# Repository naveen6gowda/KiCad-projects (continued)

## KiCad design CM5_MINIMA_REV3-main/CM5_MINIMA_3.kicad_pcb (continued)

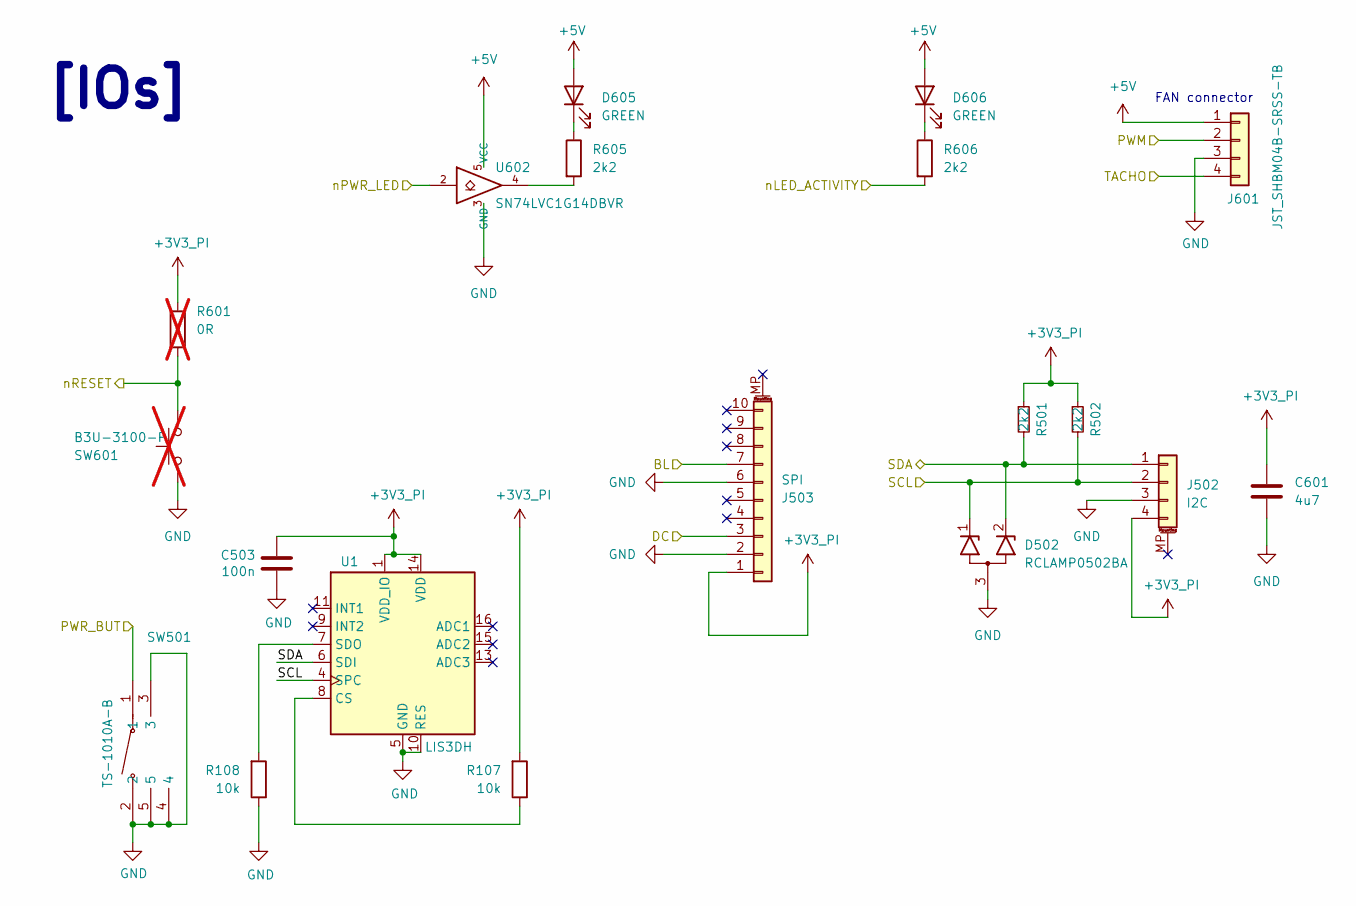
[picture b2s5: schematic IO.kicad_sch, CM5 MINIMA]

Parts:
C503: 100n; C_0402_1005Metric; Part Description 0.1uF 10% 16V Ceramic Capacitor X7R 040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
C601: 4u7; C_0805_2012Metric; Part Description 4.7uF 10% 10V Ceramic Capacitor X7R 080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
D502: RCLAMP0502BA; SOT-416
D605, D606: GREEN; LED-SMD_L1.7-W0.6-RD
J502: I2C; JST_SH_BM04B-SRSS-TB_1x04-1MP_P1.00mm_Vertical
J503: SPI; JST_SUR_BM10B-SURS-TF_1x10-1MP_P0.80mm_Vertical
J601: JST_SHBM04B-SRSS-TB; JST_SH_BM04B-SRSS-TB_1x04-1MP_P1.00mm_Vertical; Part Description 4 pin vertical 1mm pitch connector
R107, R108: 10k; R_0402_1005Metric
R501, R502, R605, R606: 2k2; R_0402_1005Metric
R601: 0R; R_0402_1005Metric; not fitted
SW501: TS-1010A-B; SW-SMD_TS-1010A-B; LCSC Part C381059
SW601: B3U-3100-P; SW_SPST_B3U-3100P-B; not fitted
U1: LIS3DH; LGA-16_3x3mm_P0.5mm_LayoutBorder3x5y
U602: SN74LVC1G14DBVR; SOT-353_SC-70-5; Part Description Buffer, Non-Inverting 1 Element 1 Bit p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

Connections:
+3V3_PI: C503.1, C601.1, J502.4, J503.1, R107.2, R501.1, R502.1, R601.1, U1.1 (VDD_IO), U1.14 (VDD); also elsewhere on the board
+5V: D605.2 (A), D606.2 (A), J601.1, U602.5 (VCC); also elsewhere on the board
/CM5/BL_GPIO24: J503.7; also elsewhere on the board
/CM5/DC_GPI25: J503.3; also elsewhere on the board
/CM5/PI_nLED_PWR: U602.2; also elsewhere on the board
/CM5/PWM: J601.2; also elsewhere on the board
/CM5/PWR_BUT: SW501.1; also elsewhere on the board
/CM5/TACHO: J601.4; also elsewhere on the board
/CM5/nLED_ACTIVITY: R606.2; also elsewhere on the board
/IO/SCL: D502.1 (K1), J502.2, R502.2, U1.4 (SPC); also elsewhere on the board
/IO/SDA: D502.2 (K2), J502.1, R501.2, U1.6 (SDI); also elsewhere on the board
unnamed: D605.1 (K), R605.1
unnamed: D606.1 (K), R606.1
unnamed: R601.2, SW601.1
unnamed: R605.2, U602.4
unnamed: R107.1, U1.8 (CS)
unnamed: R108.2, U1.7 (SDO)

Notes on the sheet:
[IOs]
FAN connector

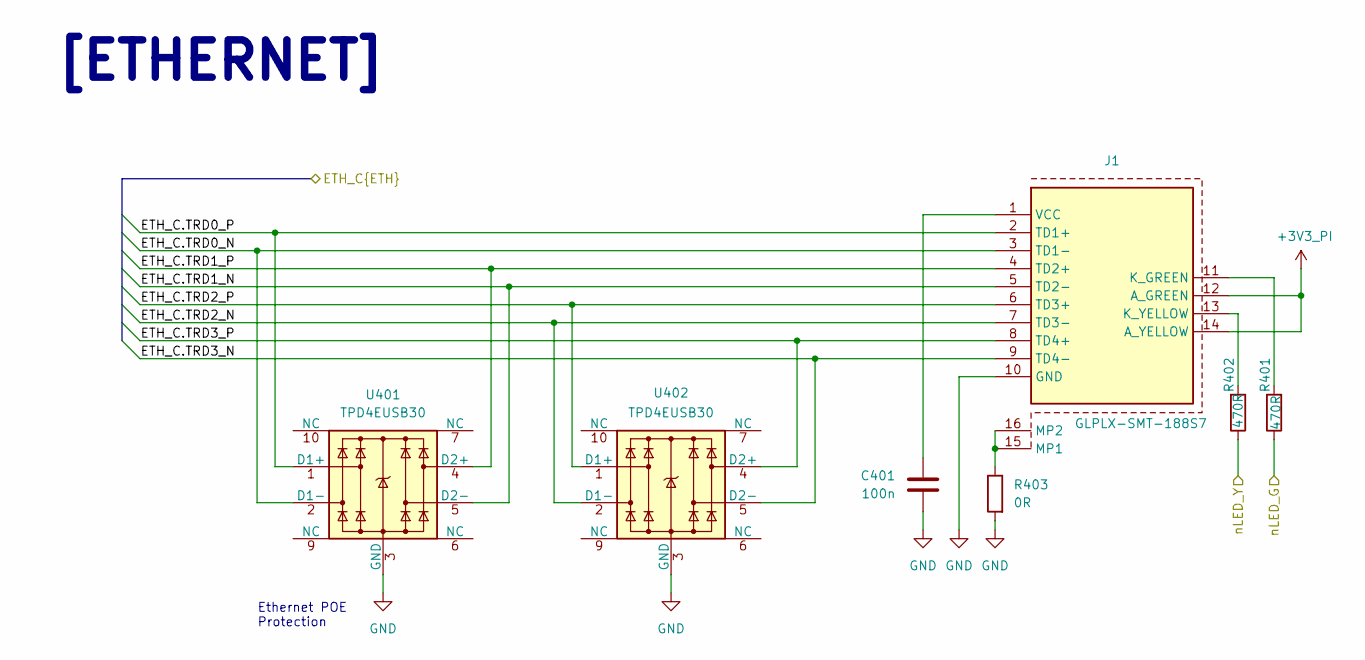
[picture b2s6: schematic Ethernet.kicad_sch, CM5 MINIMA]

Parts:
C401: 100n; C_0402_1005Metric; Part Description 0.1uF 10% 16V Ceramic Capacitor X7R 040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
J1: GLPLX-SMT-188S7; GLPLXSMT188S7QQYG; Manufacturer_Part_Number GLPLX-SMT-188S7-QQ-Y/G; Mouser Part Number 806-GLPLXSMT188S7-YG
R401, R402: 470R; R_0402_1005Metric; LCSC C25117
R403: 0R; R_0402_1005Metric
U401, U402: TPD4EUSB30; USON-10_2.5x1.0mm_P0.5mm; Part Description Quad TVS diode for high speed signals (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

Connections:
+3V3_PI: J1.12 (A_GREEN), J1.14 (A_YELLOW); also elsewhere on the board
/CM5/ETH_PI.TRD0_N: J1.3 (TD1-), U401.2 (D1-), U401.9 (NC); also elsewhere on the board
/CM5/ETH_PI.TRD0_P: J1.2 (TD1+), U401.1 (D1+), U401.10 (NC); also elsewhere on the board
/CM5/ETH_PI.TRD1_N: J1.5 (TD2-), U401.5 (D2-), U401.6 (NC); also elsewhere on the board
/CM5/ETH_PI.TRD1_P: J1.4 (TD2+), U401.4 (D2+), U401.7 (NC); also elsewhere on the board
/CM5/ETH_PI.TRD2_N: J1.7 (TD3-), U402.2 (D1-), U402.9 (NC); also elsewhere on the board
/CM5/ETH_PI.TRD2_P: J1.6 (TD3+), U402.1 (D1+), U402.10 (NC); also elsewhere on the board
/CM5/ETH_PI.TRD3_N: J1.9 (TD4-), U402.5 (D2-), U402.6 (NC); also elsewhere on the board
/CM5/ETH_PI.TRD3_P: J1.8 (TD4+), U402.4 (D2+), U402.7 (NC); also elsewhere on the board
/CM5/ETH_nLED_ACTIVITY: R401.1; also elsewhere on the board
/CM5/nLED_SPEED_100_1000: R402.1; also elsewhere on the board
unnamed: J1.11 (K_GREEN), R401.2
unnamed: J1.13 (K_YELLOW), R402.2
unnamed: J1.15 (MP1), J1.16 (MP2), R403.1
unnamed: C401.1, J1.1 (VCC)

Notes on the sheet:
[ETHERNET]
Ethernet POE Protection

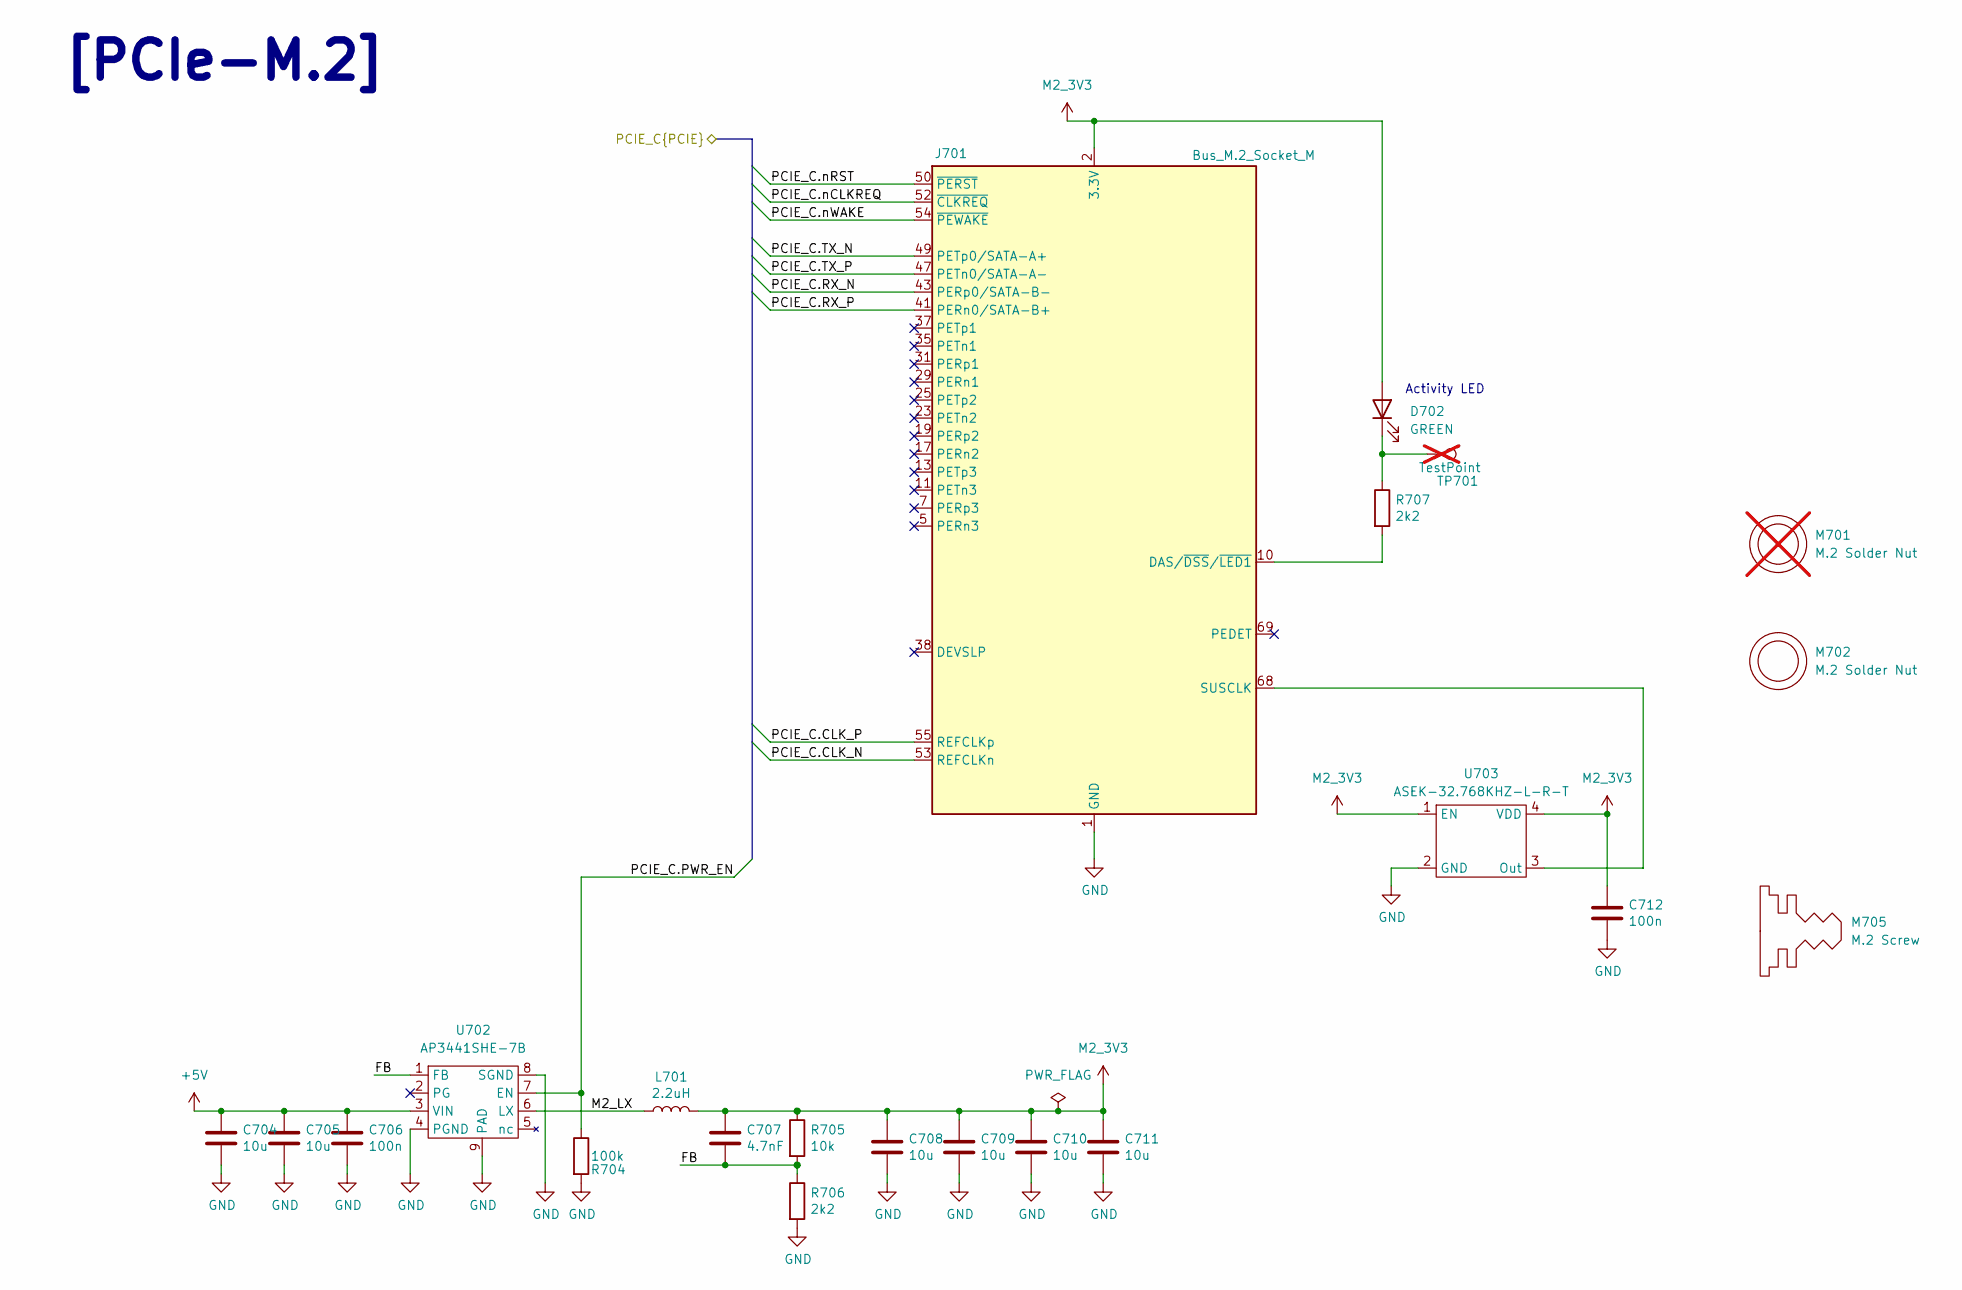
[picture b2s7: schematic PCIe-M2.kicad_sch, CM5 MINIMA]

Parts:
C704, C705, C708, C709, C710, C711: 10u; C_0805_2012Metric; Part Description 10uF 10% 10V Ceramic Capacitor X7R 0805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; LCSC C15850
C706, C712: 100n; C_0402_1005Metric; Part Description 0.1uF 10% 16V Ceramic Capacitor X7R 040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
C707: 4.7nF; C_0402_1005Metric; Part Description 4.7nF capacitor 0402
D702: GREEN; LED-SMD_L1.7-W0.6-RD
J701: Bus_M.2_Socket_M; M.2 M Key socket_2230_2242; Part Description M.2 M Key connector
L701: 2.2uH; L_Coilcraft_XAL5030-XXX; Part Description Inductor, SMT, 2u2, IRMS=7A, ISAT=8.1A,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; LCSC C920280
M701: M.2 Solder Nut; MountingHole_3mm_Pad; Part Description Solder nut for M.2 slot; not fitted
M702: M.2 Solder Nut; MountingHole_3mm_Pad; Part Description Solder nut for M.2 slot
M705: M.2 Screw; Part Description M.2 Screw
R704: 100k; R_0402_1005Metric; LCSC C25741
R705: 10k; R_0402_1005Metric; LCSC C25744
R706: 2k2; R_0402_1005Metric
R707: 2k2; R_0402_1005Metric; Part Description Resistor 1K M1005 1% 63mW
TP701: TestPoint; TestPoint_Pad_2.0x2.0mm; Part Description Test point; not fitted
U702: AP3441SHE-7B; DFN-8-1EP_2x2mm_P0.5mm_EP1.05x1.75mm; Part Description 3A DC-DC converter
U703: ASEK-32.768KHZ-L-R-T; Crystal_SMD_3225-4Pin_3.2x2.5mm; Part Description 32KHz Xtal oscilator

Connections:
+5V: C704.1, C705.1, C706.1, U702.3 (VIN); also elsewhere on the board
/CM5/PCIE_PI.CLK_N: J701.53 (REFCLKn); also elsewhere on the board
/CM5/PCIE_PI.CLK_P: J701.55 (REFCLKp); also elsewhere on the board
/CM5/PCIE_PI.PWR_EN: R704.1, U702.7 (EN); also elsewhere on the board
/CM5/PCIE_PI.RX_N: J701.43 (PETp0); also elsewhere on the board
/CM5/PCIE_PI.RX_P: J701.41 (PETn0); also elsewhere on the board
/CM5/PCIE_PI.TX_N: J701.49 (PERp0); also elsewhere on the board
/CM5/PCIE_PI.TX_P: J701.47 (PERn0); also elsewhere on the board
/CM5/PCIE_PI.nCLKREQ: J701.52 (~CLKREQ); also elsewhere on the board
/CM5/PCIE_PI.nRST: J701.50 (~PERST); also elsewhere on the board
/CM5/PCIE_PI.nWAKE: J701.54 (~PEWAKE); also elsewhere on the board
/PCIe-M2/FB: C707.2, R705.2, R706.1, U702.1 (FB)
/PCIe-M2/M2_LX: L701.1, U702.6 (LX)
M2_3V3: C707.1, C708.1, C709.1, C710.1, C711.1, C712.1, D702.2 (A), J701.2 (3.3V), J701.4 (3.3V), J701.12 (3.3V), J701.14 (3.3V), J701.16 (3.3V), J701.18 (3.3V), J701.70 (3.3V), J701.72 (3.3V), J701.74 (3.3V), L701.2, R705.1, U703.1 (EN), U703.4 (VDD)
unnamed: D702.1 (K), R707.1, TP701.1
unnamed: J701.10 (DAS/~DSS/~LED1), R707.2
unnamed: J701.68 (SUSCLK), U703.3 (Out)

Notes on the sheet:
[PCIe-M.2]
Activity LED

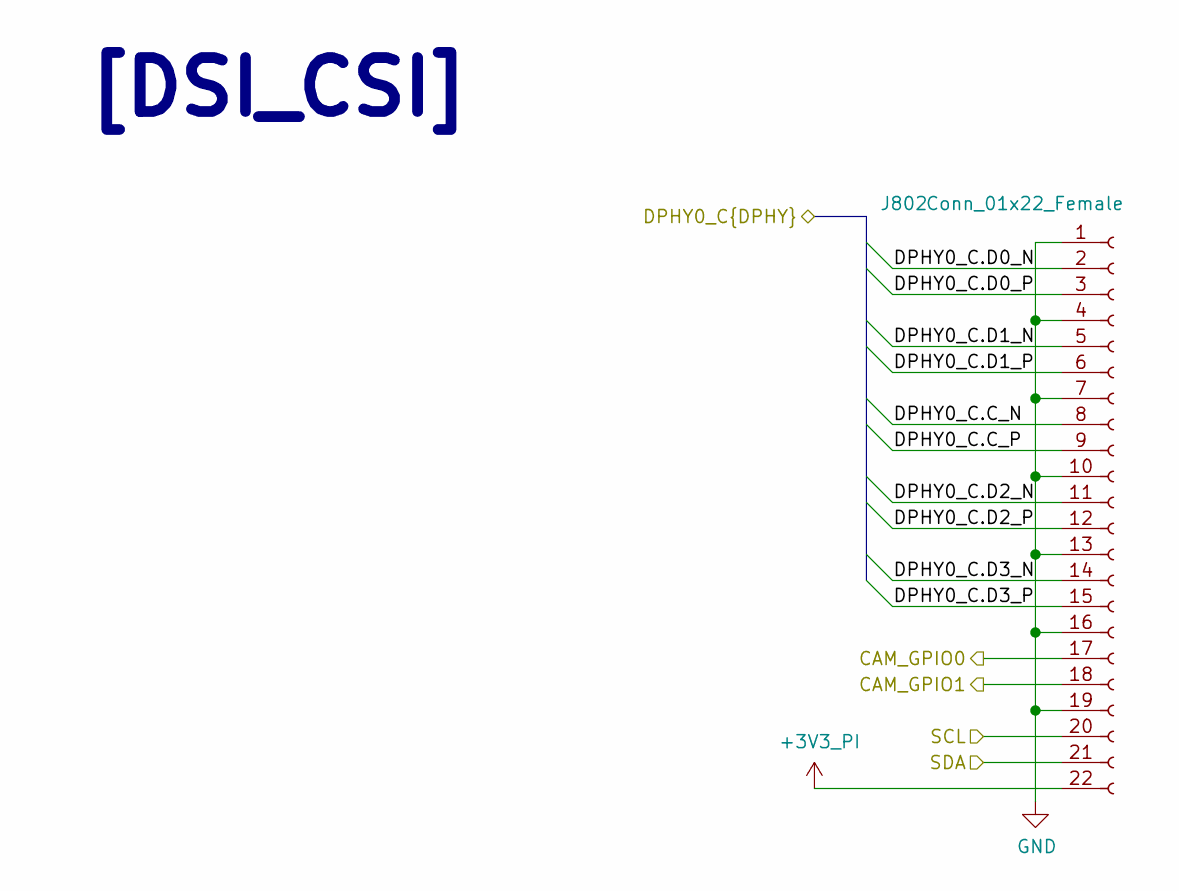
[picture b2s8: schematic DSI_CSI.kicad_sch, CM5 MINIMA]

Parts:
J802: Conn_01x22_Female; Hirose_FH12-22S-0.5SH_1x22-1MP_P0.50mm_Horizontal; Part Description 22 Position FFC, FPC Connector Contacts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

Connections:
+3V3_PI: J802.22; also elsewhere on the board
/CM5/CAM_GPIO0: J802.17; also elsewhere on the board
/CM5/CAM_GPIO1: J802.18; also elsewhere on the board
/CM5/DPHY0_P.C_N: J802.8; also elsewhere on the board
/CM5/DPHY0_P.C_P: J802.9; also elsewhere on the board
/CM5/DPHY0_P.D0_N: J802.2; also elsewhere on the board
/CM5/DPHY0_P.D0_P: J802.3; also elsewhere on the board
/CM5/DPHY0_P.D1_N: J802.5; also elsewhere on the board
/CM5/DPHY0_P.D1_P: J802.6; also elsewhere on the board
/CM5/DPHY0_P.D2_N: J802.11; also elsewhere on the board
/CM5/DPHY0_P.D2_P: J802.12; also elsewhere on the board
/CM5/DPHY0_P.D3_N: J802.14; also elsewhere on the board
/CM5/DPHY0_P.D3_P: J802.15; also elsewhere on the board
/CM5/SCL0: J802.20; also elsewhere on the board
/CM5/SDA0: J802.21; also elsewhere on the board

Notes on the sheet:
[DSI_CSI]

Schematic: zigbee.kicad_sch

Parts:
J2: Conn_01x04_Pin; PinHeader_1x05_P1.27mm_Vertical
R1, R2: 10k; R_0402_1005Metric
U2: MGM240LD22VIF2; MGM240L_SIL

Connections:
+3V3_PI: J2.1, R1.1, R2.1, U2.13 (VDD); also elsewhere on the board
/CM5/BOOT_GPIO17: R2.2, U2.4 (PA04); also elsewhere on the board
/CM5/CS_GPIO18: U2.16 (PC03); also elsewhere on the board
/CM5/IRQ_GPIO26: R1.2, U2.8 (PD00); also elsewhere on the board
/CM5/MISO_GPIO19: U2.15 (PC02); also elsewhere on the board
/CM5/MOSI_GPIO20: U2.10 (PC01); also elsewhere on the board
/CM5/RST_GPIO27: U2.11 (RESET); also elsewhere on the board
/CM5/SCLK_GPIO21: U2.9 (PC00); also elsewhere on the board
/Zigbee_Thread/SWCLK: J2.3, U2.1 (PA01)
/Zigbee_Thread/SWDIO: J2.2, U2.2 (PA02)
/Zigbee_Thread/SWO: J2.5, U2.3 (PA03)

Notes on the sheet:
[Zigbee_Thread]

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
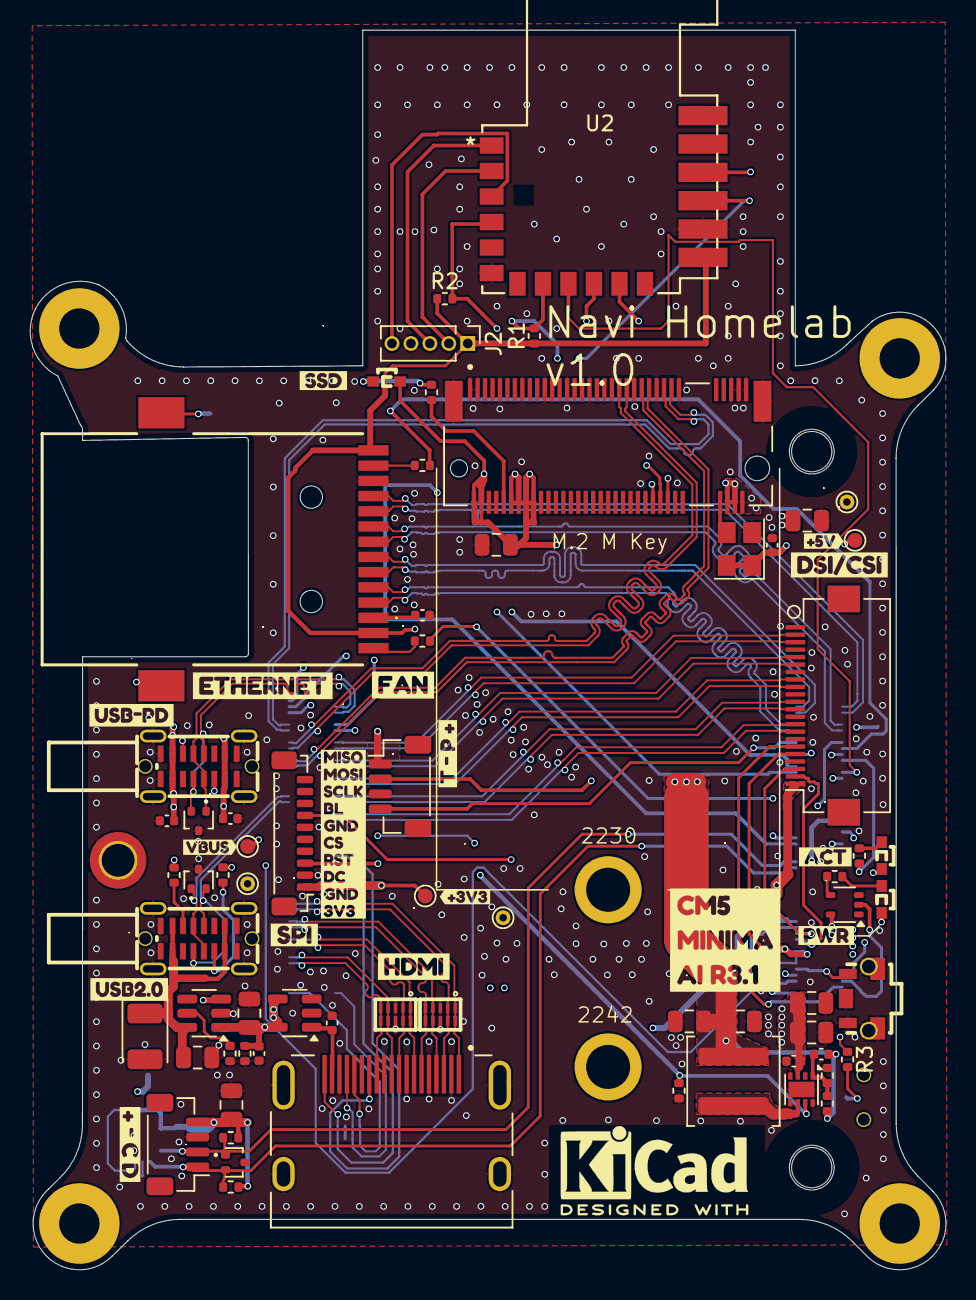
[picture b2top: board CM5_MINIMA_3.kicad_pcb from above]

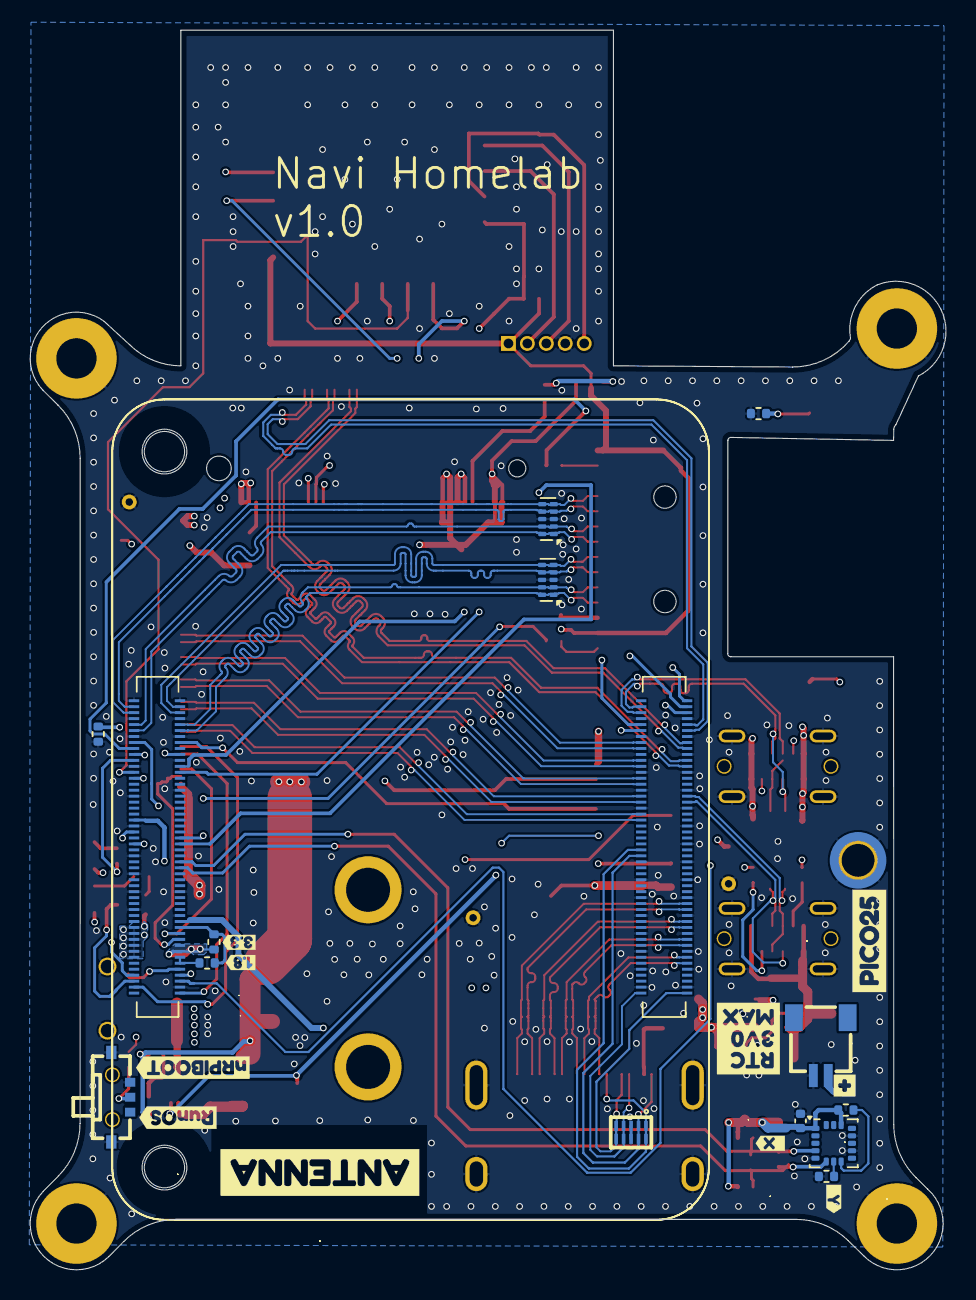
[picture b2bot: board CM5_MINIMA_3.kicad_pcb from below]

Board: 6 copper layers, 61.4 x 83.1 mm, 116 parts (25 on the bottom side), 100 nets.

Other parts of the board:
kibuzzard-67CC6BA6: G***; kibuzzard-67CC6BA6
kibuzzard-67CC6BD3: G***; kibuzzard-67CC6BD3
kibuzzard-67CC6D9E: G***; kibuzzard-67CC6D9E
kibuzzard-67CC6D94: G***; kibuzzard-67CC6D94
kibuzzard-67CC7445: G***; kibuzzard-67CC7445
kibuzzard-67EBAC4C: G***; kibuzzard-67EBAC4C
kibuzzard-67EBB9C1: G***; kibuzzard-67EBB9C1
kibuzzard-67EBD21C: G***; kibuzzard-67EBD21C
kibuzzard-67EBD221: G***; kibuzzard-67EBD221
kibuzzard-67EBEF55: G***; kibuzzard-67EBEF55
kibuzzard-67EBF0A0: G***; kibuzzard-67EBF0A0
kibuzzard-67EBF14E: G***; kibuzzard-67EBF14E
kibuzzard-67EBF015: G***; kibuzzard-67EBF015
kibuzzard-675DA838: G***; kibuzzard-675DA838
kibuzzard-675DA850: G***; kibuzzard-675DA850
kibuzzard-675DA866: G***; kibuzzard-675DA866
kibuzzard-675EDCA4: G***; kibuzzard-675EDCA4
kibuzzard-675EDCB9: G***; kibuzzard-675EDCB9
kibuzzard-6772D327: G***; kibuzzard-6772D327
kibuzzard-6772DA33: G***; kibuzzard-6772DA33
kibuzzard-6773B9CA: G***; kibuzzard-6773B9CA
kibuzzard-6773B9F7: G***; kibuzzard-6773B9F7
kibuzzard-6773BA89: G***; kibuzzard-6773BA89
kibuzzard-6773C2D7: G***; kibuzzard-6773C2D7
kibuzzard-6773C222: G***; kibuzzard-6773C222
kibuzzard-6773C376: G***; kibuzzard-6773C376
kibuzzard-67795592: G***; kibuzzard-67795592

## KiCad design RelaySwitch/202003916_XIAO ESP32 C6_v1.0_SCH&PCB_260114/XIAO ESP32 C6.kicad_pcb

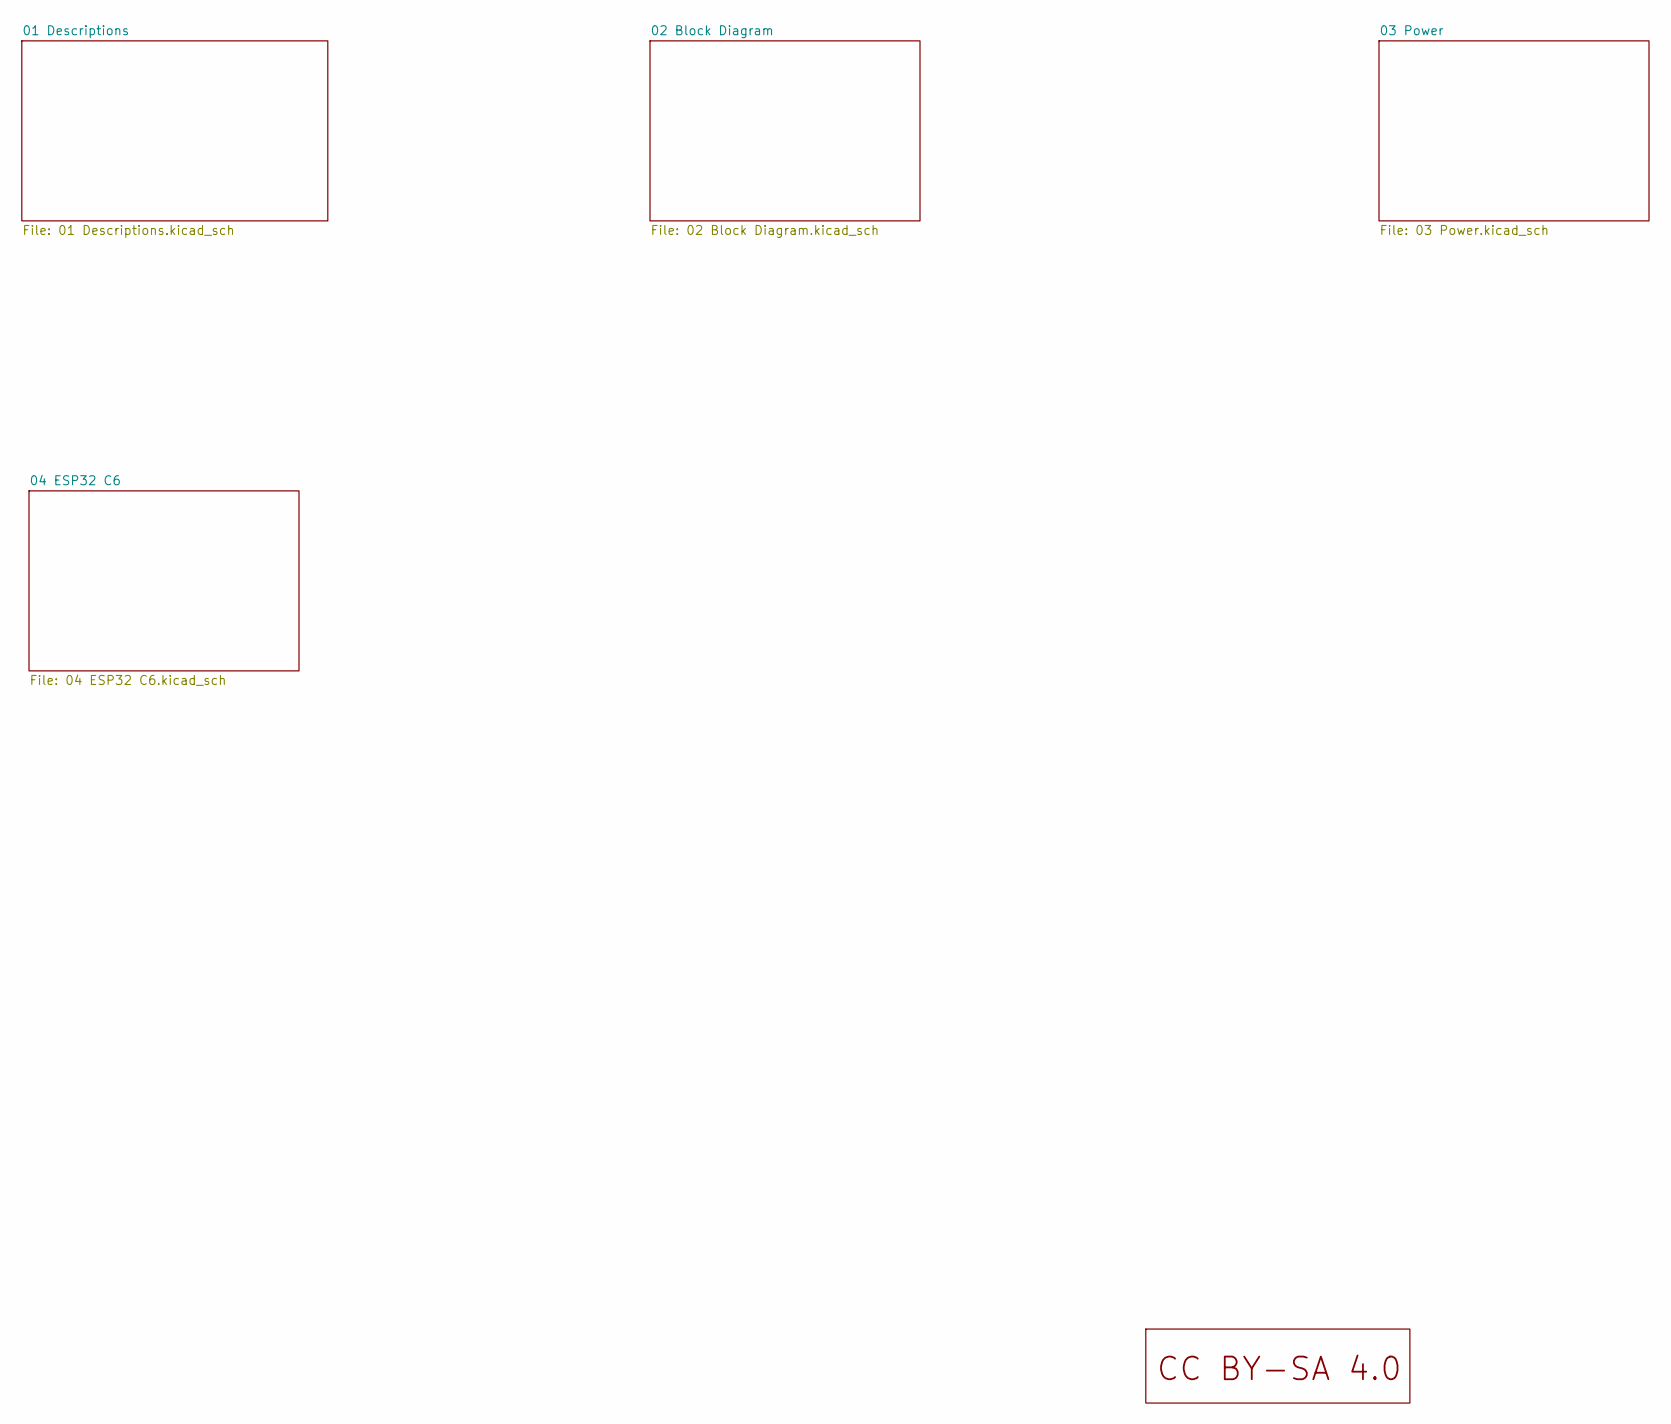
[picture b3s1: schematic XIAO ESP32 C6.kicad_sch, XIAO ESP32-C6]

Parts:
U6: LOGO_CC_BY-SA_4.0

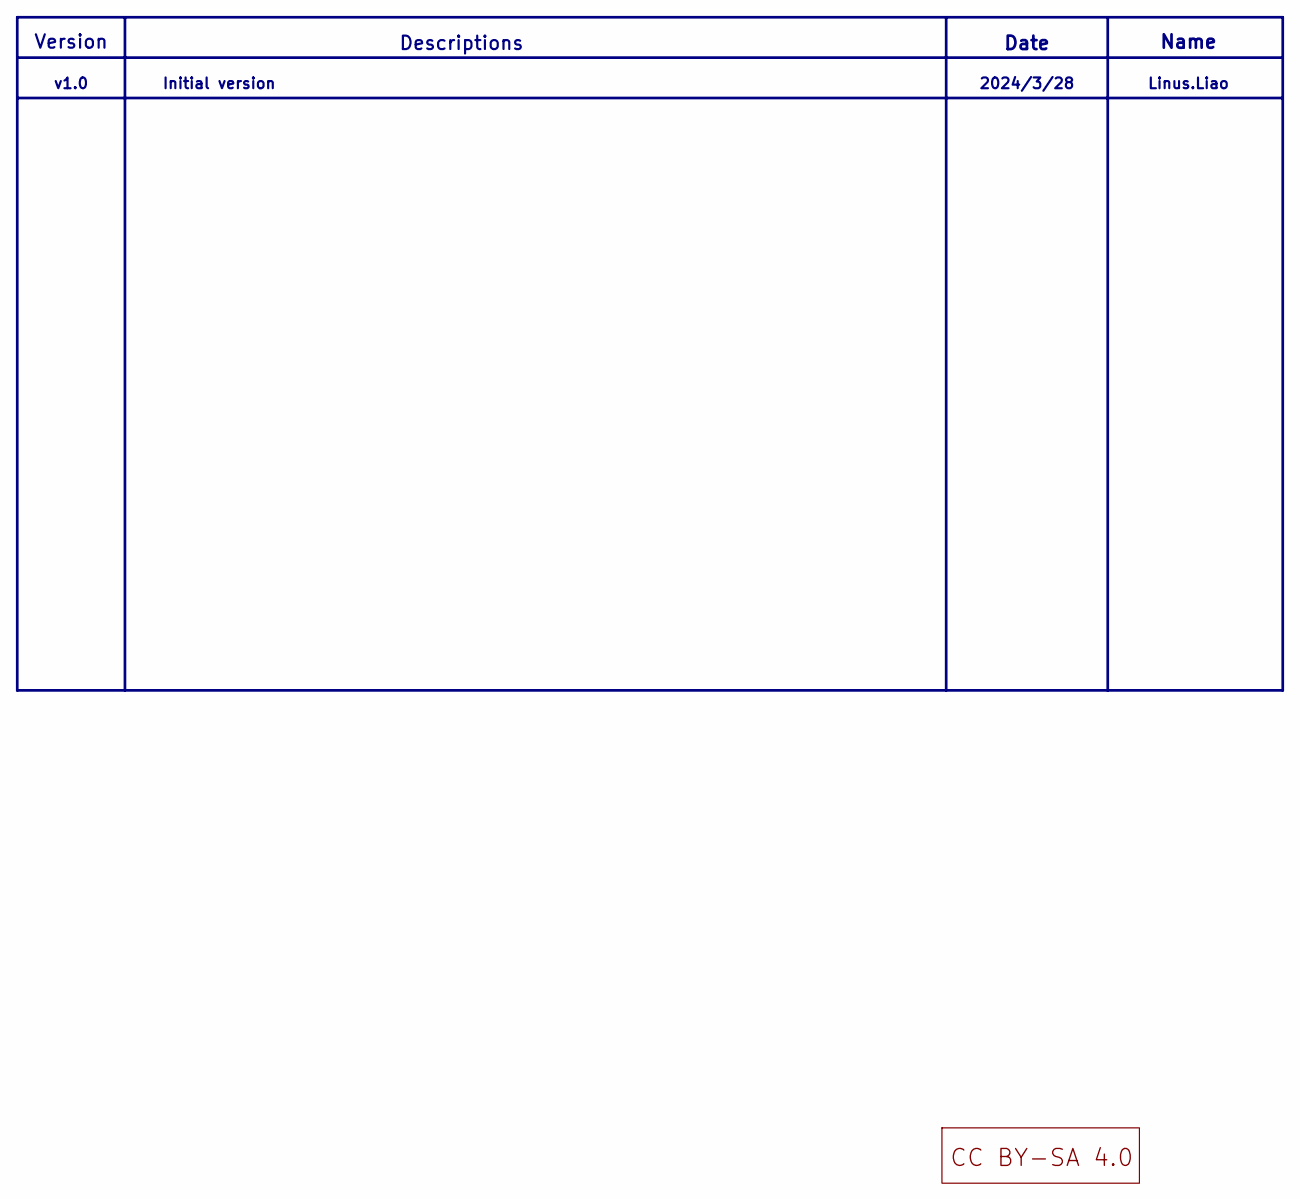
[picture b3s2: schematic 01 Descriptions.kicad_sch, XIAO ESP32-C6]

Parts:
U7: LOGO_CC_BY-SA_4.0

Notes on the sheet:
Date
Descriptions
Linus.Liao
2024/3/28
v1.0
Initial version
Name
Version

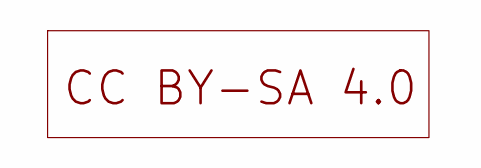
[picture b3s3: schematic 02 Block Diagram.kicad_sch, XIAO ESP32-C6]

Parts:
U8: LOGO_CC_BY-SA_4.0
